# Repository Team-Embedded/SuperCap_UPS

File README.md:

<!--
 * @Author: JunQiLiu
 * @Date: 2020-11-16 19:04:18
 * @LastEditTime: 2020-11-28 10:25:53
 * @Description: 
 * @FilePath: \undefinedc:\Users\JunQiLiu\Documents\SuperCap_UPS\README.md
 * @ 
-->
# SuperCap_UPS
UPS solution based on super capacitor

## Description
* This is a super capacitor UPS,which really has all the UPS functions include a supercapacitor charger and a boost converter,under normal conditions, the input power supply can directly supply power to the load,and when input power is not available,the super capacitor UPS can provide backup power.
* **This project is currently in testing**

## Hardware Design
The core of this board is **LTC4041**,a power management IC.

> The LTC4041 is a complete supercapacitor backup system for 2.9V to 5.5V supply rails. It contains a high current step-down DC/DC converter to charge a single supercapacitor or two supercapacitors in series. When input power is unavailable, the step-down regulator operates in reverse as a step-up regulator to backup the system output from the supercapacitor(s).

you can visit this website to see details: [LTC4041](https://www.analog.com/en/products/ltc4041.html#product-overview)

For test the functions of this IC,I drew the schematic with reference to the official document.

## Calculating Holdup or Backup Time
[Energy Storage Using Supercapacitors: How Big Is Big Enough?](https://www.analog.com/en/analog-dialogue/raqs/raq-issue-179.html)

## Design Tools
 A Cross Platform and Open Source Electronics Design Automation Suite : [KiCad](https://kicad.org/)

 ## TODO
- [ ] make a PCB 
- [ ] function test

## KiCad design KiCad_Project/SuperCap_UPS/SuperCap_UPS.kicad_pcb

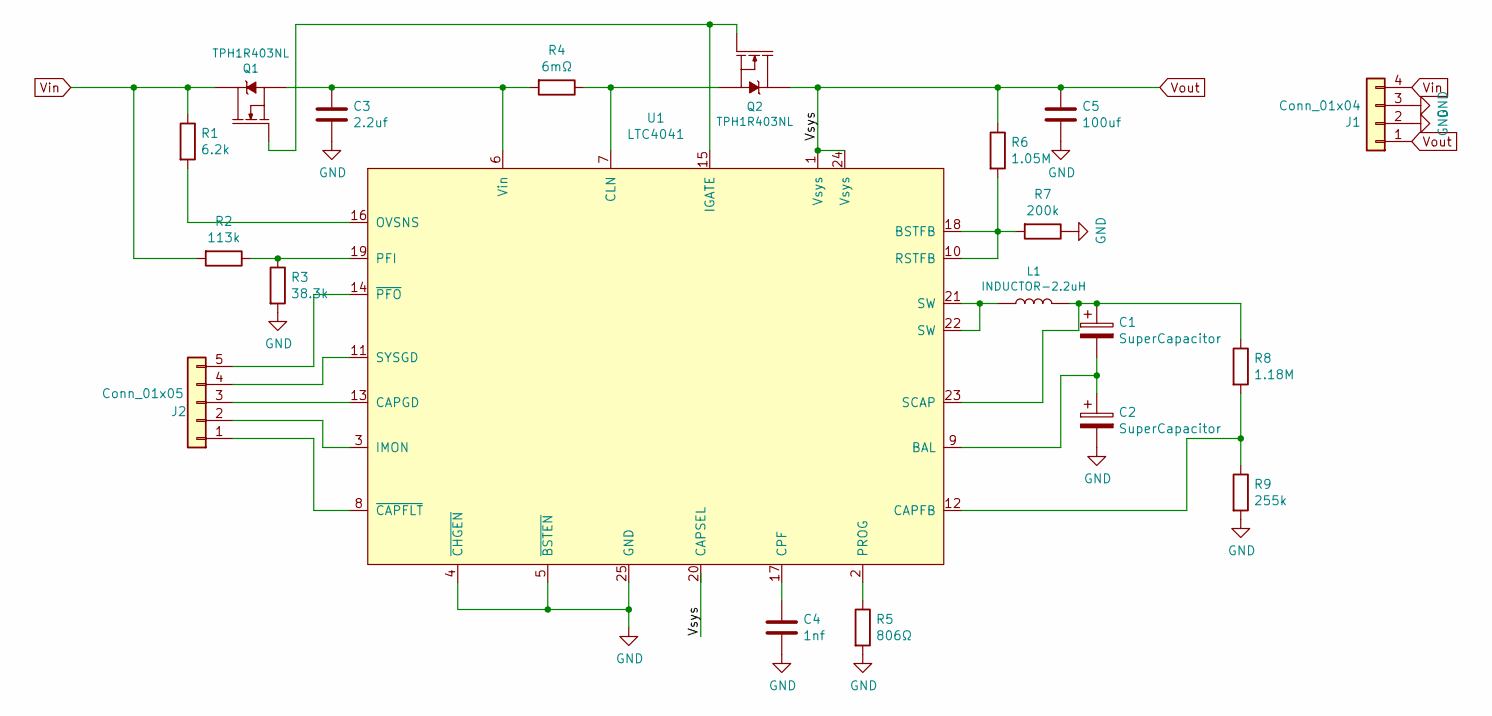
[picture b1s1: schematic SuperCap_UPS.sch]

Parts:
C1, C2: SuperCapacitor
C3: 2.2uf; C_1210_3225Metric
C4: 1nf; C_0603_1608Metric
C5: 100uf; C_1210_3225Metric
J1: Conn_01x04; PhoenixContact_MC_1,5_4-G-3.5_1x04_P3.50mm_Horizontal
J2: Conn_01x05; PinHeader_1x05_P2.54mm_Vertical
L1: INDUCTOR-2.2uH; 74477810
Q1, Q2: TPH1R403NL; SOP-Advance-8
R1: 6.2k; R_0603_1608Metric
R2: 113k; R_0603_1608Metric
R3: 38.3k; R_0603_1608Metric
R4: 6mΩ; R_2512_6332Metric
R5: 806Ω; R_0603_1608Metric
R6: 1.05M; R_0603_1608Metric
R7: 200k; R_0603_1608Metric
R8: 1.18M; R_0603_1608Metric
R9: 255k; R_0603_1608Metric
U1: LTC4041

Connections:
GND: C2.2, C3.2, C4.2, C5.2, J1.2, J1.3, R3.2, R5.2, R7.1, R9.2, U1.4 (~CHGEN), U1.5 (~BSTEN), U1.25 (GND)
unnamed: C1.1, L1.2, R8.1, U1.23 (SCAP)
unnamed: C1.2, C2.1, U1.9 (BAL)
unnamed: C3.1, Q1.2 (S), R4.2, U1.6 (Vin)
unnamed: C4.1, U1.17 (CPF)
unnamed: J2.1, U1.8 (~CAPFLT)
unnamed: J2.2, U1.3 (IMON)
unnamed: J2.3, U1.13 (CAPGD)
unnamed: J2.4, U1.11 (SYSGD)
unnamed: J2.5, U1.14 (~PFO)
unnamed: L1.1, U1.21 (SW), U1.22 (SW)
unnamed: Q1.1 (G), Q2.1 (G), U1.15 (IGATE)
unnamed: Q2.2 (S), R4.1, U1.7 (CLN)
unnamed: R1.2, U1.16 (OVSNS)
unnamed: R2.1, R3.1, U1.19 (PFI)
unnamed: R5.1, U1.2 (PROG)
unnamed: R6.2, R7.2, U1.10 (RSTFB), U1.18 (BSTFB)
unnamed: R8.2, R9.1, U1.12 (CAPFB)
Vin: J1.4, Q1.3 (D), R1.1, R2.2
Vout: C5.1, J1.1, Q2.3 (D), R6.1, U1.1 (Vsys), U1.24 (Vsys)

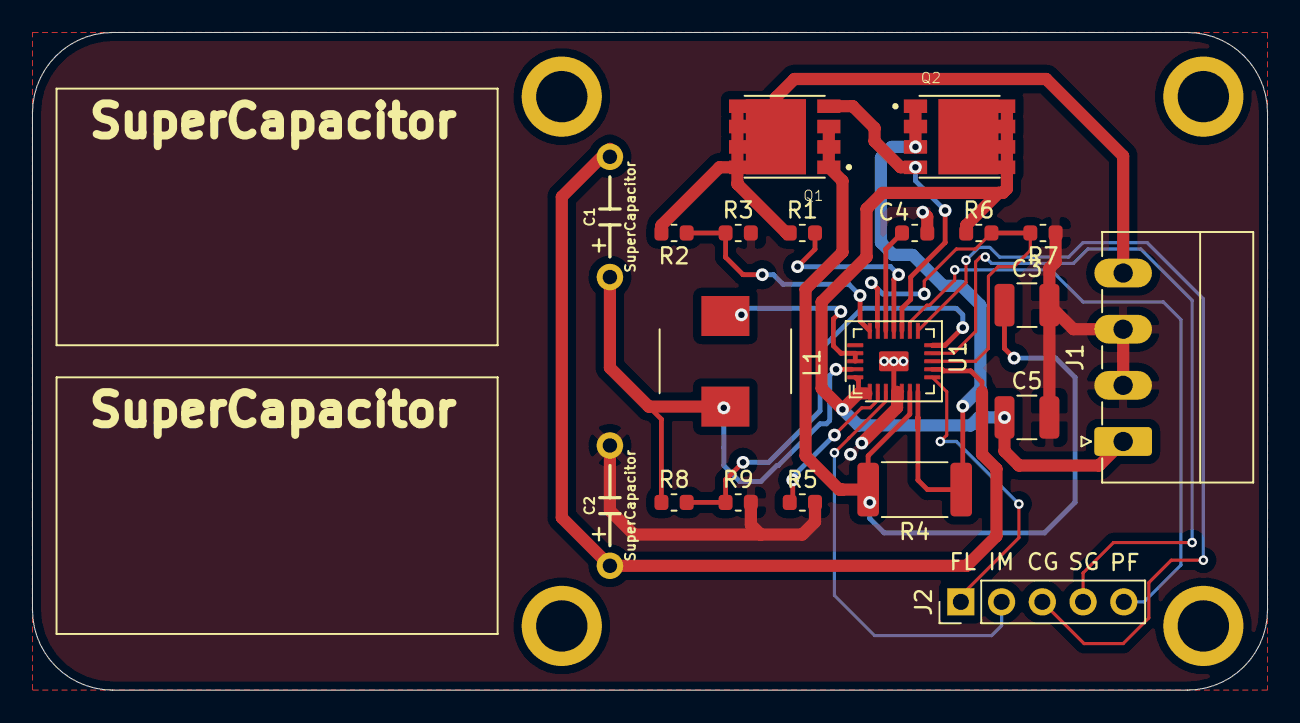
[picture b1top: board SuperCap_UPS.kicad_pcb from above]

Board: 2 copper layers, 77.0 x 41.0 mm, 20 parts (0 on the bottom side), 20 nets.

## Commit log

2020-11-16 doc: 添加资料
2020-11-25 feat: add KiCAD PCB files
2020-11-25 doc: update README
2020-11-25 doc: mosfet
2020-12-01 feat: 功能引脚
2020-12-07 feat: 添加gerber文件

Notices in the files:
README.md:
License: Apache
